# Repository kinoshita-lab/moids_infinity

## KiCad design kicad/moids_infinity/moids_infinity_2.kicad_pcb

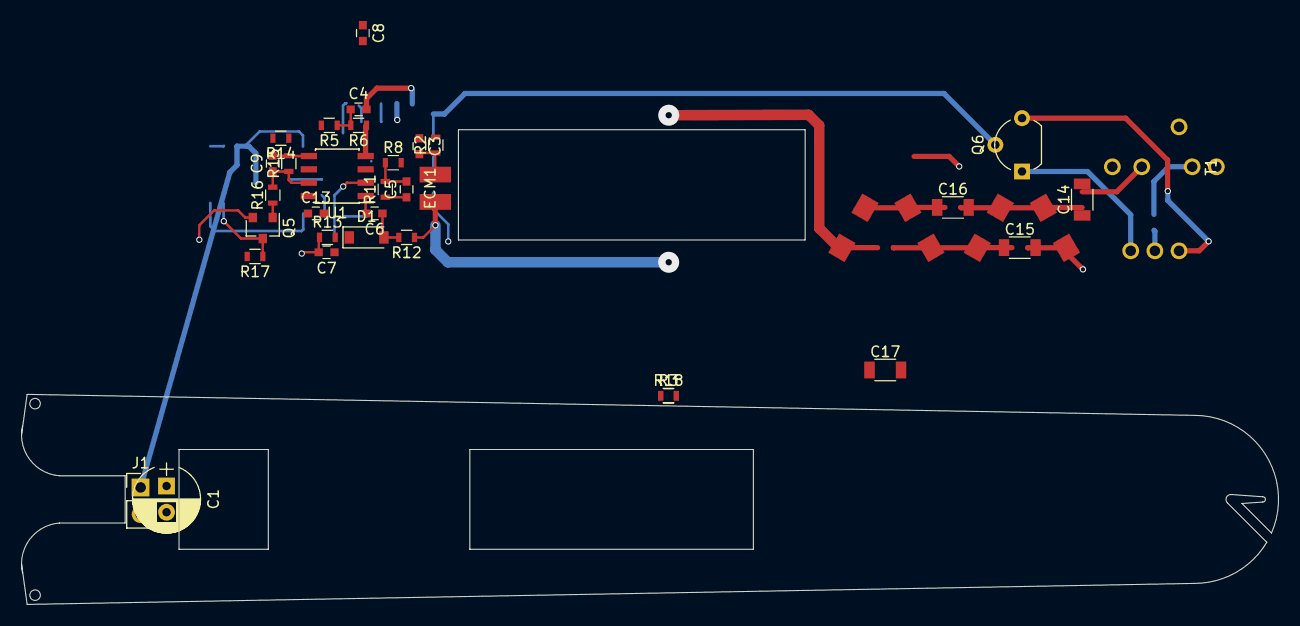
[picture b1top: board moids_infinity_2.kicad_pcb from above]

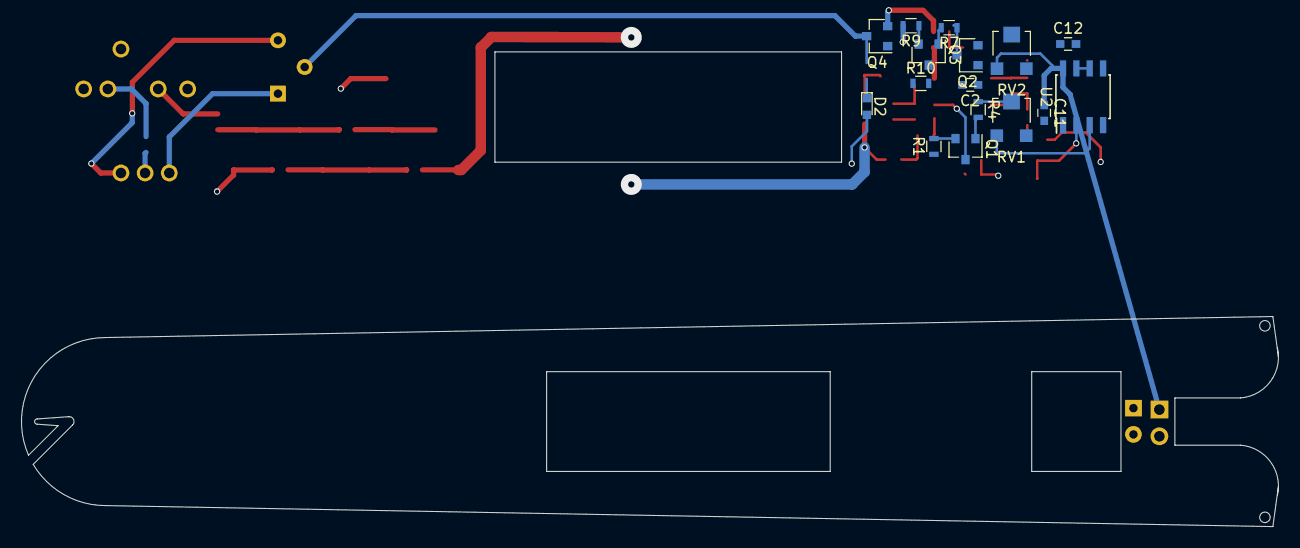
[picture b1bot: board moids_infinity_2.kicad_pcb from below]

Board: 2 copper layers, 119.7 x 45.2 mm, 53 parts (16 on the bottom side), 33 nets.

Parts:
C1: 470u; CP_Radial_D6.3mm_P2.50mm
C2, C13: 10u; C_0603
C3, C4, C6, C7, C8, C11, C12: 0.1u; C_0603
C5, C9: 560p; C_0603
C14, C15, C16, C17: 2200p; C_1206
D1: D; D_SOD-123
D2: LED; LED_0603
D3, D4, D5, D6: D; DO-214AC
ECM1: ECM_C9767; CONDENCER_MICROPHONE_C9767
J1: Conn_01x02; Pin_Header_Straight_1x02_Pitch2.54mm
Q1: 2sc33s5-y; SOT-23
Q2, Q5: 2sc3325-y; SOT-23
Q3: 2sa1313; SOT-23
Q4: SSM3K329R; SOT-23
Q6: Q_NPN_ECB; TO-92_Molded_Wide
R1, R3, R6, R7, R14, R16: 1k; R_0603
R2, R4, R5, R8, R17: 10k; R_0603
R9, R10, R12, R15: 1M; R_0603
R11, R13: 100k; R_0603
R18: 200; R_0603
RV1: 330k; Potentiometer_Trimmer-TSR-C3305
RV2: 10k; Potentiometer_Trimmer-TSR-C3305
T1: digit_junk_trans; digit_junk_transformer
U1: LMV358; SOIC-8_3.9x4.9mm_Pitch1.27mm
U2: NE555; SOIC-8_3.9x4.9mm_Pitch1.27mm

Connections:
+5V: C1.1, C7.1, C11.1, J1.1, R2.2, R4.2, R8.2, R17.2, R18.2, RV2.1, T1.2, U1.8, U2.8
unnamed: C2.1, Q2.1, R3.1, RV1.2
unnamed: C3.1, R7.2
unnamed: C3.2, ECM1.1, R2.1
unnamed: C4.1, R4.1, R5.2, U1.3
unnamed: C5.1, C6.2, R10.1, U1.1
unnamed: C6.1, D1.2, R11.2
unnamed: C8.1, D1.1, R12.2, U1.5
unnamed: C9.1, R15.1, R16.2, U1.7
unnamed: C9.2, R13.2, R15.2, U1.6
unnamed: C12.2, U2.5
unnamed: C13.2, RV2.2, U2.6, U2.7
unnamed: C14.1, C16.2, D3.1, D4.2
unnamed: C15.1, C17.2, D4.1, D5.2
unnamed: C17.1, D6.1
unnamed: D2.1, R14.2
unnamed: Q1.1, R3.2
unnamed: Q1.2, R1.2
unnamed: Q2.3, R6.1
unnamed: Q3.1, R6.2
unnamed: Q3.2, R8.1
unnamed: Q3.3, Q4.1, R9.2
unnamed: Q5.1, R16.1
unnamed: Q5.3, R17.1, U2.2
unnamed: Q6.1, T1.5
unnamed: Q6.3, T1.7
unnamed: R18.1, T1.6
jacob_terminal_1: C16.1, D5.1, D6.2
jacob_terminal_2: C1.2, C2.2, C4.2, C7.2, C8.2, C11.2, C12.1, C13.1, ECM1.2, J1.2, Q2.2, Q4.2, Q5.2, R1.1, R5.1, R9.1, R11.1, R12.1, R13.1, U1.4, U2.1
mute: C5.2, Q1.3, R7.1, R10.2, U1.2
spark_gate: C15.2, D3.2, Q4.3, Q6.2, R14.1
timer_out: RV1.1, U2.3
transformer_out: C14.2, T1.3

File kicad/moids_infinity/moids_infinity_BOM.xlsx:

Library | Part | Footprint | Value | Number | Reference
conn | Conn_01x02_Male | Pin_Headers:Pin_Header_Straight_1x02_Pitch2.54mm | Conn_01x02 | 1 | J1
device | C | Capacitors_SMD:C_0603 | 0.1u | 7 | C11, C4, C7, C12, C6, C3, C8
device | C | Capacitors_SMD:C_0603 | 10u | 2 | C13, C2
device | C | Capacitors_SMD:C_0603 | 560p | 2 | C5, C9
device | C | Capacitors_SMD:C_1206 | 2200p | 4 | C14, C15, C17, C16
device | CP | Capacitors_THT:CP_Radial_D6.3mm_P2.50mm | 470u | 1 | C1
device | D | Diodes_SMD:D_SOD-123 | D | 1 | D1
device | D | custom_pcb_footprints:DO-214AC | D | 4 | D3, D4, D5, D6
device | LED | LEDs:LED_0603 | LED | 1 | D2
device | POT | custom_pcb_footprints:Potentiometer_Trimmer-TSR-C3305 | 10k | 1 | RV2
device | POT | custom_pcb_footprints:Potentiometer_Trimmer-TSR-C3305 | 330k | 1 | RV1
device | Q_NMOS_GSD | TO_SOT_Packages_SMD:SOT-23 | SSM3K329R | 1 | Q4
device | Q_NPN_ECB | TO_SOT_Packages_THT:TO-92_Inline_Narrow_Oval | Q_NPN_ECB | 1 | Q6
device | R | Resistors_SMD:R_0603 | 100k | 2 | R13, R11
device | R | Resistors_SMD:R_0603 | 10k | 5 | R8, R17, R2, R5, R4
device | R | Resistors_SMD:R_0603 | 1M | 4 | R12, R15, R10, R9
device | R | Resistors_SMD:R_0603 | 1k | 6 | R3, R16, R14, R7, R6, R1
device | R | Resistors_SMD:R_0603 | 200 | 1 | R18
device | TEST | Pin_Headers:Pin_Header_Straight_1x01_Pitch1.00mm | TEST | 1 | TP1
device | TEST | custom_pcb_footprints:SolderWirePad_single_SMD_1.5x3mm | TERMINAL | 2 | JT2, JT1
linear | LMV358 | Housings_SOIC:SOIC-8_3.9x4.9mm_Pitch1.27mm | LMV358 | 1 | U1
linear | NE555 | Housings_SOIC:SOIC-8_3.9x4.9mm_Pitch1.27mm | NE555 | 1 | U2
moids_infinity | ECM_C9767 | custom_pcb_footprints:CONDENCER_MICROPHONE_C9767 | ECM_C9767 | 1 | ECM1
moids_infinity-rescue | digit_junk_trans-RESCUE-moids_infinity | custom_pcb_footprints:digit_junk_transformer | digit_junk_trans | 1 | T1
transistors | BC817 | TO_SOT_Packages_SMD:SOT-23 | 2sc3325-y | 2 | Q2, Q5
transistors | BC817 | TO_SOT_Packages_SMD:SOT-23 | 2sc33s5-y | 1 | Q1
transistors | BC856 | TO_SOT_Packages_SMD:SOT-23 | 2sa1313 | 1 | Q3

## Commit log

2019-01-21 add moids_infinity files almost as-is
2019-08-09 add spark schematics
2019-08-09 add board
